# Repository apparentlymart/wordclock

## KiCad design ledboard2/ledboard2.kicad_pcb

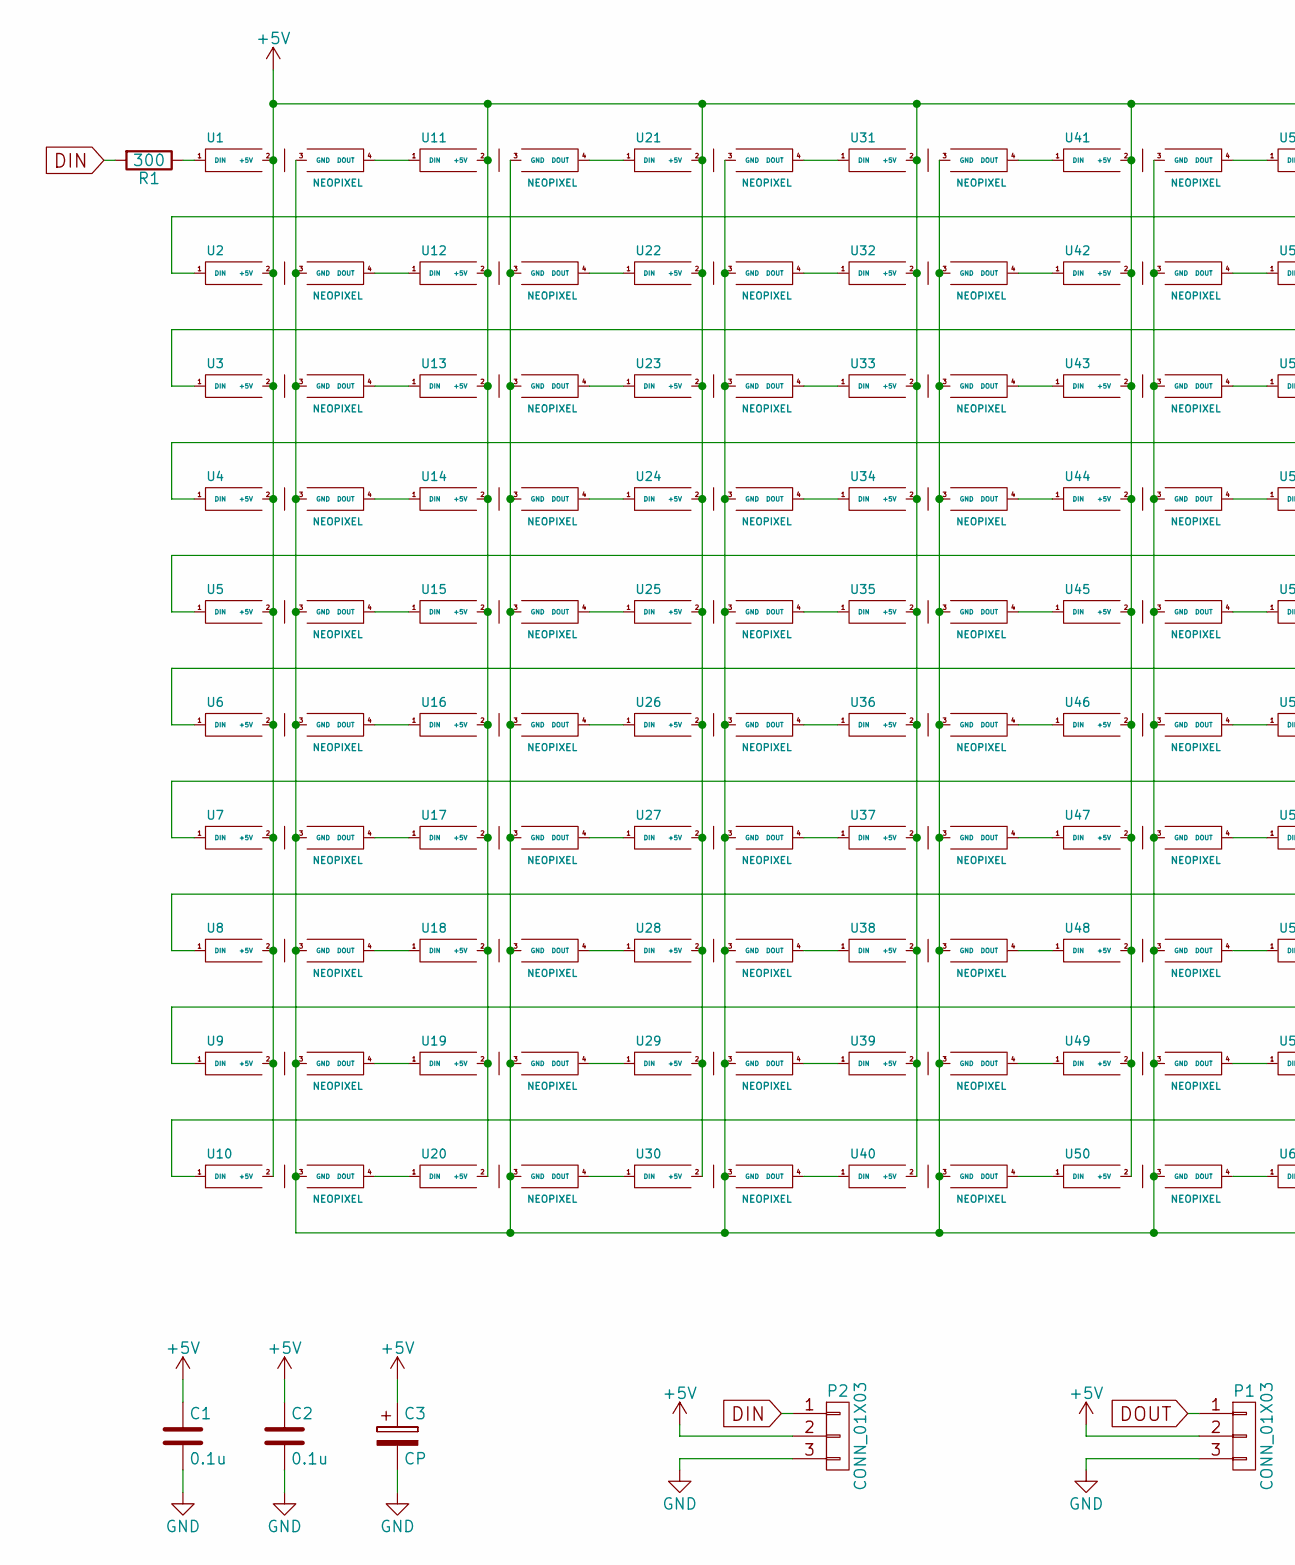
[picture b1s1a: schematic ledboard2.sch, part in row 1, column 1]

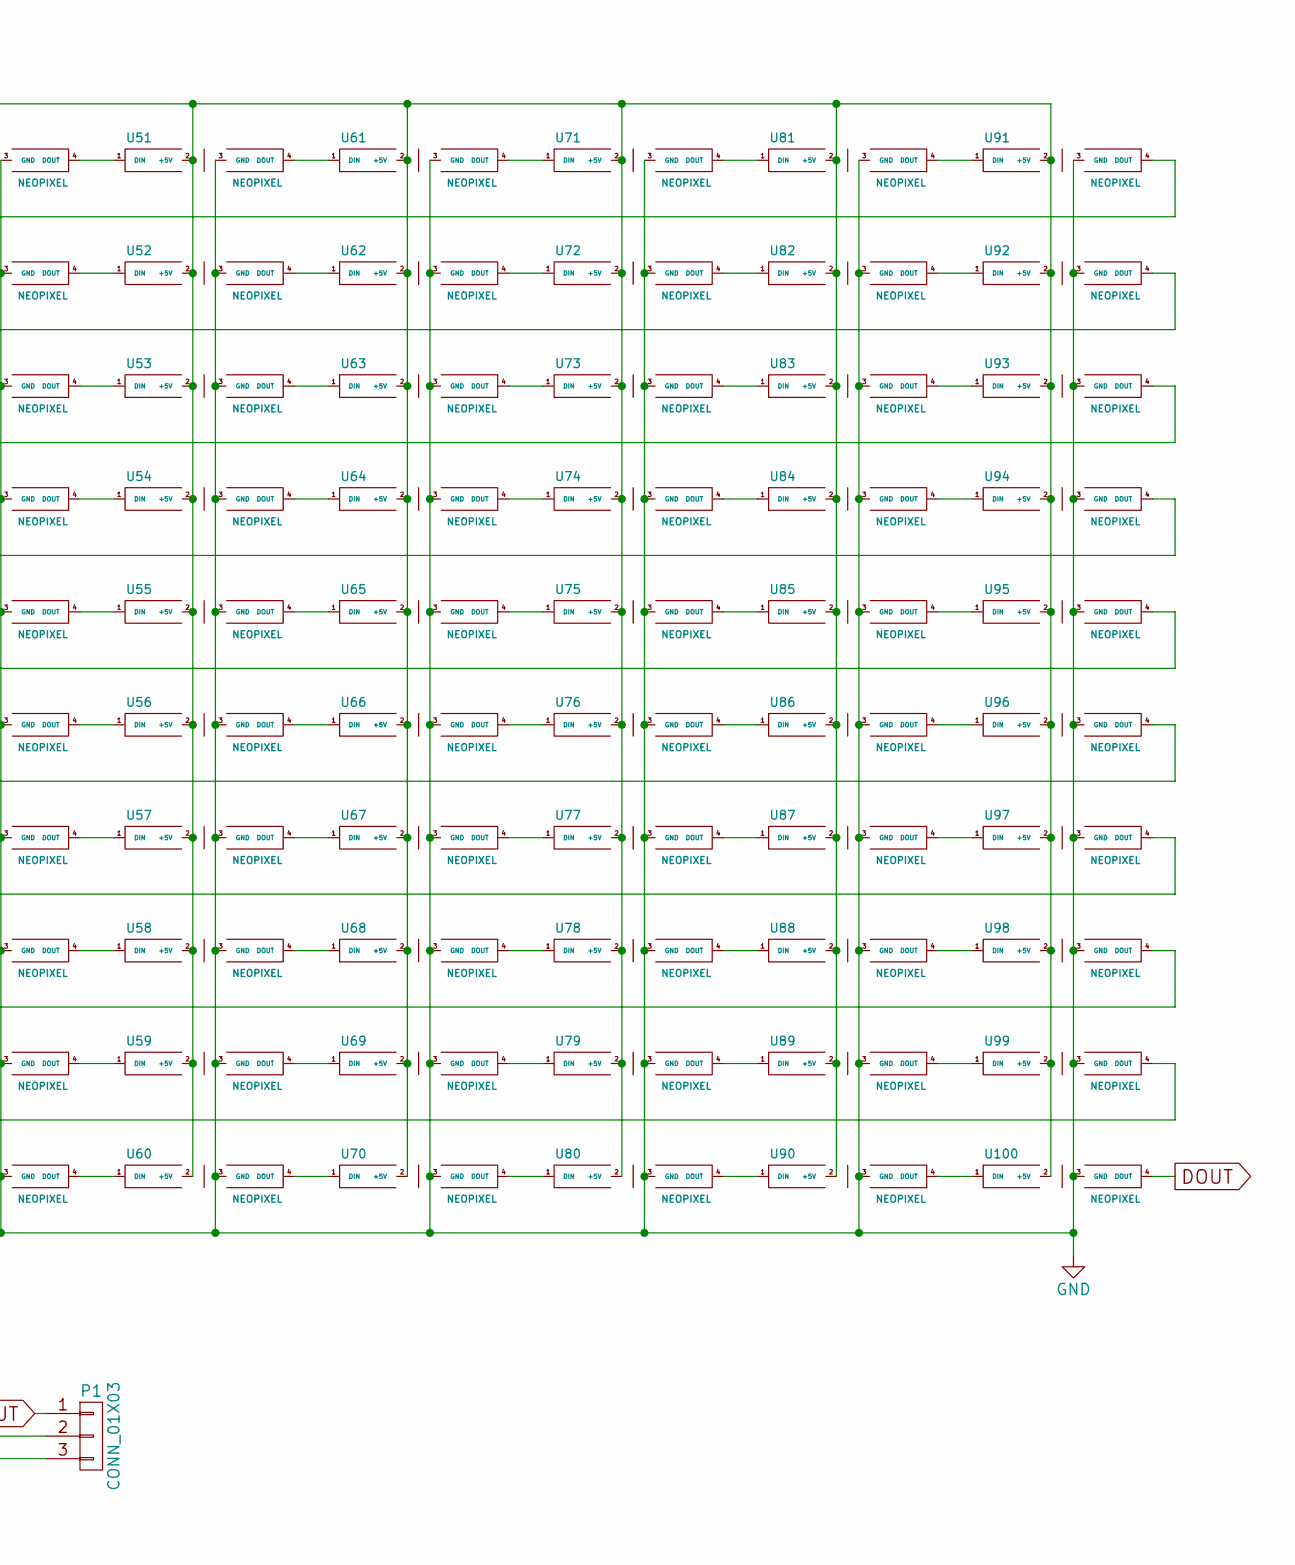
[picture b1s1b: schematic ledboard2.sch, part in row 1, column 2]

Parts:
C1, C2: 0.1u; C_0805_HandSoldering
C3: CP
P1, P2: CONN_01X03; Pin_Header_Straight_1x03
R1: 300; R_0805_HandSoldering
U1, U2, U3, U4, U5, U6, U7, U8, U9, U10, U11, U12, U13, U14, U15, U16, U17, U18, U19, U20, U21, U22, U23, U24, U25, U26, U27, U28, U29, U30, U31, U32, U33, U34, U35, U36, U37, U38, U39, U40, U41, U42, U43, U44, U45, U46, U47, U48, U49, U50, U51, U52, U53, U54, U55, U56, U57, U58, U59, U60, U61, U62, U63, U64, U65, U66, U67, U68, U69, U70, U71, U72, U73, U74, U75, U76, U77, U78, U79, U80, U81, U82, U83, U84, U85, U86, U87, U88, U89, U90, U91, U92, U93, U94, U95, U96, U97, U98, U99, U100: NEOPIXEL; NEOPIXEL_8MM

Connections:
+5V: C1.1, C2.1, C3.1, P1.2, P2.2, U1.2 (+5V), U2.2 (+5V), U3.2 (+5V), U4.2 (+5V), U5.2 (+5V), U6.2 (+5V), U7.2 (+5V), U8.2 (+5V), U9.2 (+5V), U10.2 (+5V), U11.2 (+5V), U12.2 (+5V), U13.2 (+5V), U14.2 (+5V), U15.2 (+5V), U16.2 (+5V), U17.2 (+5V), U18.2 (+5V), U19.2 (+5V), U20.2 (+5V), U21.2 (+5V), U22.2 (+5V), U23.2 (+5V), U24.2 (+5V), U25.2 (+5V), U26.2 (+5V), U27.2 (+5V), U28.2 (+5V), U29.2 (+5V), U30.2 (+5V), U31.2 (+5V), U32.2 (+5V), U33.2 (+5V), U34.2 (+5V), U35.2 (+5V), U36.2 (+5V), U37.2 (+5V), U38.2 (+5V), U39.2 (+5V), U40.2 (+5V), U41.2 (+5V), U42.2 (+5V), U43.2 (+5V), U44.2 (+5V), U45.2 (+5V), U46.2 (+5V), U47.2 (+5V), U48.2 (+5V), U49.2 (+5V), U50.2 (+5V), U51.2 (+5V), U52.2 (+5V), U53.2 (+5V), U54.2 (+5V), U55.2 (+5V), U56.2 (+5V), U57.2 (+5V), U58.2 (+5V), U59.2 (+5V), U60.2 (+5V), U61.2 (+5V), U62.2 (+5V), U63.2 (+5V), U64.2 (+5V), U65.2 (+5V), U66.2 (+5V), U67.2 (+5V), U68.2 (+5V), U69.2 (+5V), U70.2 (+5V), U71.2 (+5V), U72.2 (+5V), U73.2 (+5V), U74.2 (+5V), U75.2 (+5V), U76.2 (+5V), U77.2 (+5V), U78.2 (+5V), U79.2 (+5V), U80.2 (+5V), U81.2 (+5V), U82.2 (+5V), U83.2 (+5V), U84.2 (+5V), U85.2 (+5V), U86.2 (+5V), U87.2 (+5V), U88.2 (+5V), U89.2 (+5V), U90.2 (+5V), U91.2 (+5V), U92.2 (+5V), U93.2 (+5V), U94.2 (+5V), U95.2 (+5V), U96.2 (+5V), U97.2 (+5V), U98.2 (+5V), U99.2 (+5V), U100.2 (+5V)
DIN: P2.1, R1.2
DOUT: P1.1, U100.4 (DOUT)
GND: C1.2, C2.2, C3.2, P1.3, P2.3, U1.3 (GND), U2.3 (GND), U3.3 (GND), U4.3 (GND), U5.3 (GND), U6.3 (GND), U7.3 (GND), U8.3 (GND), U9.3 (GND), U10.3 (GND), U11.3 (GND), U12.3 (GND), U13.3 (GND), U14.3 (GND), U15.3 (GND), U16.3 (GND), U17.3 (GND), U18.3 (GND), U19.3 (GND), U20.3 (GND), U21.3 (GND), U22.3 (GND), U23.3 (GND), U24.3 (GND), U25.3 (GND), U26.3 (GND), U27.3 (GND), U28.3 (GND), U29.3 (GND), U30.3 (GND), U31.3 (GND), U32.3 (GND), U33.3 (GND), U34.3 (GND), U35.3 (GND), U36.3 (GND), U37.3 (GND), U38.3 (GND), U39.3 (GND), U40.3 (GND), U41.3 (GND), U42.3 (GND), U43.3 (GND), U44.3 (GND), U45.3 (GND), U46.3 (GND), U47.3 (GND), U48.3 (GND), U49.3 (GND), U50.3 (GND), U51.3 (GND), U52.3 (GND), U53.3 (GND), U54.3 (GND), U55.3 (GND), U56.3 (GND), U57.3 (GND), U58.3 (GND), U59.3 (GND), U60.3 (GND), U61.3 (GND), U62.3 (GND), U63.3 (GND), U64.3 (GND), U65.3 (GND), U66.3 (GND), U67.3 (GND), U68.3 (GND), U69.3 (GND), U70.3 (GND), U71.3 (GND), U72.3 (GND), U73.3 (GND), U74.3 (GND), U75.3 (GND), U76.3 (GND), U77.3 (GND), U78.3 (GND), U79.3 (GND), U80.3 (GND), U81.3 (GND), U82.3 (GND), U83.3 (GND), U84.3 (GND), U85.3 (GND), U86.3 (GND), U87.3 (GND), U88.3 (GND), U89.3 (GND), U90.3 (GND), U91.3 (GND), U92.3 (GND), U93.3 (GND), U94.3 (GND), U95.3 (GND), U96.3 (GND), U97.3 (GND), U98.3 (GND), U99.3 (GND), U100.3 (GND)
unnamed: R1.1, U1.1 (DIN)
unnamed: U1.4 (DOUT), U11.1 (DIN)
unnamed: U2.1 (DIN), U91.4 (DOUT)
unnamed: U3.1 (DIN), U92.4 (DOUT)
unnamed: U4.1 (DIN), U93.4 (DOUT)
unnamed: U5.1 (DIN), U94.4 (DOUT)
unnamed: U6.1 (DIN), U95.4 (DOUT)
unnamed: U7.1 (DIN), U96.4 (DOUT)
unnamed: U8.1 (DIN), U97.4 (DOUT)
unnamed: U9.1 (DIN), U98.4 (DOUT)
unnamed: U10.1 (DIN), U99.4 (DOUT)
unnamed: U10.4 (DOUT), U20.1 (DIN)
unnamed: U11.4 (DOUT), U21.1 (DIN)
unnamed: U2.4 (DOUT), U12.1 (DIN)
unnamed: U12.4 (DOUT), U22.1 (DIN)
unnamed: U3.4 (DOUT), U13.1 (DIN)
unnamed: U13.4 (DOUT), U23.1 (DIN)
unnamed: U4.4 (DOUT), U14.1 (DIN)
unnamed: U14.4 (DOUT), U24.1 (DIN)
unnamed: U5.4 (DOUT), U15.1 (DIN)
unnamed: U15.4 (DOUT), U25.1 (DIN)
unnamed: U6.4 (DOUT), U16.1 (DIN)
unnamed: U16.4 (DOUT), U26.1 (DIN)
unnamed: U7.4 (DOUT), U17.1 (DIN)
unnamed: U17.4 (DOUT), U27.1 (DIN)
unnamed: U8.4 (DOUT), U18.1 (DIN)
unnamed: U18.4 (DOUT), U28.1 (DIN)
unnamed: U9.4 (DOUT), U19.1 (DIN)
unnamed: U19.4 (DOUT), U29.1 (DIN)
unnamed: U20.4 (DOUT), U30.1 (DIN)
unnamed: U21.4 (DOUT), U31.1 (DIN)
unnamed: U22.4 (DOUT), U32.1 (DIN)
unnamed: U23.4 (DOUT), U33.1 (DIN)
unnamed: U24.4 (DOUT), U34.1 (DIN)
unnamed: U25.4 (DOUT), U35.1 (DIN)
unnamed: U26.4 (DOUT), U36.1 (DIN)
unnamed: U27.4 (DOUT), U37.1 (DIN)
unnamed: U28.4 (DOUT), U38.1 (DIN)
unnamed: U29.4 (DOUT), U39.1 (DIN)
unnamed: U30.4 (DOUT), U40.1 (DIN)
unnamed: U31.4 (DOUT), U41.1 (DIN)
unnamed: U32.4 (DOUT), U42.1 (DIN)
unnamed: U33.4 (DOUT), U43.1 (DIN)
unnamed: U34.4 (DOUT), U44.1 (DIN)
unnamed: U35.4 (DOUT), U45.1 (DIN)
unnamed: U36.4 (DOUT), U46.1 (DIN)
unnamed: U37.4 (DOUT), U47.1 (DIN)
unnamed: U38.4 (DOUT), U48.1 (DIN)
unnamed: U39.4 (DOUT), U49.1 (DIN)
unnamed: U40.4 (DOUT), U50.1 (DIN)
unnamed: U41.4 (DOUT), U51.1 (DIN)
unnamed: U42.4 (DOUT), U52.1 (DIN)
unnamed: U43.4 (DOUT), U53.1 (DIN)
unnamed: U44.4 (DOUT), U54.1 (DIN)
unnamed: U45.4 (DOUT), U55.1 (DIN)
unnamed: U46.4 (DOUT), U56.1 (DIN)
unnamed: U47.4 (DOUT), U57.1 (DIN)
unnamed: U48.4 (DOUT), U58.1 (DIN)
unnamed: U49.4 (DOUT), U59.1 (DIN)
unnamed: U50.4 (DOUT), U60.1 (DIN)
unnamed: U51.4 (DOUT), U61.1 (DIN)
unnamed: U52.4 (DOUT), U62.1 (DIN)
unnamed: U53.4 (DOUT), U63.1 (DIN)
unnamed: U54.4 (DOUT), U64.1 (DIN)
unnamed: U55.4 (DOUT), U65.1 (DIN)
unnamed: U56.4 (DOUT), U66.1 (DIN)
unnamed: U57.4 (DOUT), U67.1 (DIN)
unnamed: U58.4 (DOUT), U68.1 (DIN)
unnamed: U59.4 (DOUT), U69.1 (DIN)
unnamed: U60.4 (DOUT), U70.1 (DIN)
unnamed: U61.4 (DOUT), U71.1 (DIN)
unnamed: U62.4 (DOUT), U72.1 (DIN)
unnamed: U63.4 (DOUT), U73.1 (DIN)
unnamed: U64.4 (DOUT), U74.1 (DIN)
unnamed: U65.4 (DOUT), U75.1 (DIN)
unnamed: U66.4 (DOUT), U76.1 (DIN)
unnamed: U67.4 (DOUT), U77.1 (DIN)
unnamed: U68.4 (DOUT), U78.1 (DIN)
unnamed: U69.4 (DOUT), U79.1 (DIN)
unnamed: U70.4 (DOUT), U80.1 (DIN)
unnamed: U71.4 (DOUT), U81.1 (DIN)
unnamed: U72.4 (DOUT), U82.1 (DIN)
unnamed: U73.4 (DOUT), U83.1 (DIN)
unnamed: U74.4 (DOUT), U84.1 (DIN)
unnamed: U75.4 (DOUT), U85.1 (DIN)
unnamed: U76.4 (DOUT), U86.1 (DIN)
unnamed: U77.4 (DOUT), U87.1 (DIN)
unnamed: U78.4 (DOUT), U88.1 (DIN)
unnamed: U79.4 (DOUT), U89.1 (DIN)
unnamed: U80.4 (DOUT), U90.1 (DIN)
unnamed: U81.4 (DOUT), U91.1 (DIN)
unnamed: U82.4 (DOUT), U92.1 (DIN)
unnamed: U83.4 (DOUT), U93.1 (DIN)
unnamed: U84.4 (DOUT), U94.1 (DIN)
unnamed: U85.4 (DOUT), U95.1 (DIN)
unnamed: U86.4 (DOUT), U96.1 (DIN)
unnamed: U87.4 (DOUT), U97.1 (DIN)
unnamed: U88.4 (DOUT), U98.1 (DIN)
unnamed: U89.4 (DOUT), U99.1 (DIN)
unnamed: U90.4 (DOUT), U100.1 (DIN)

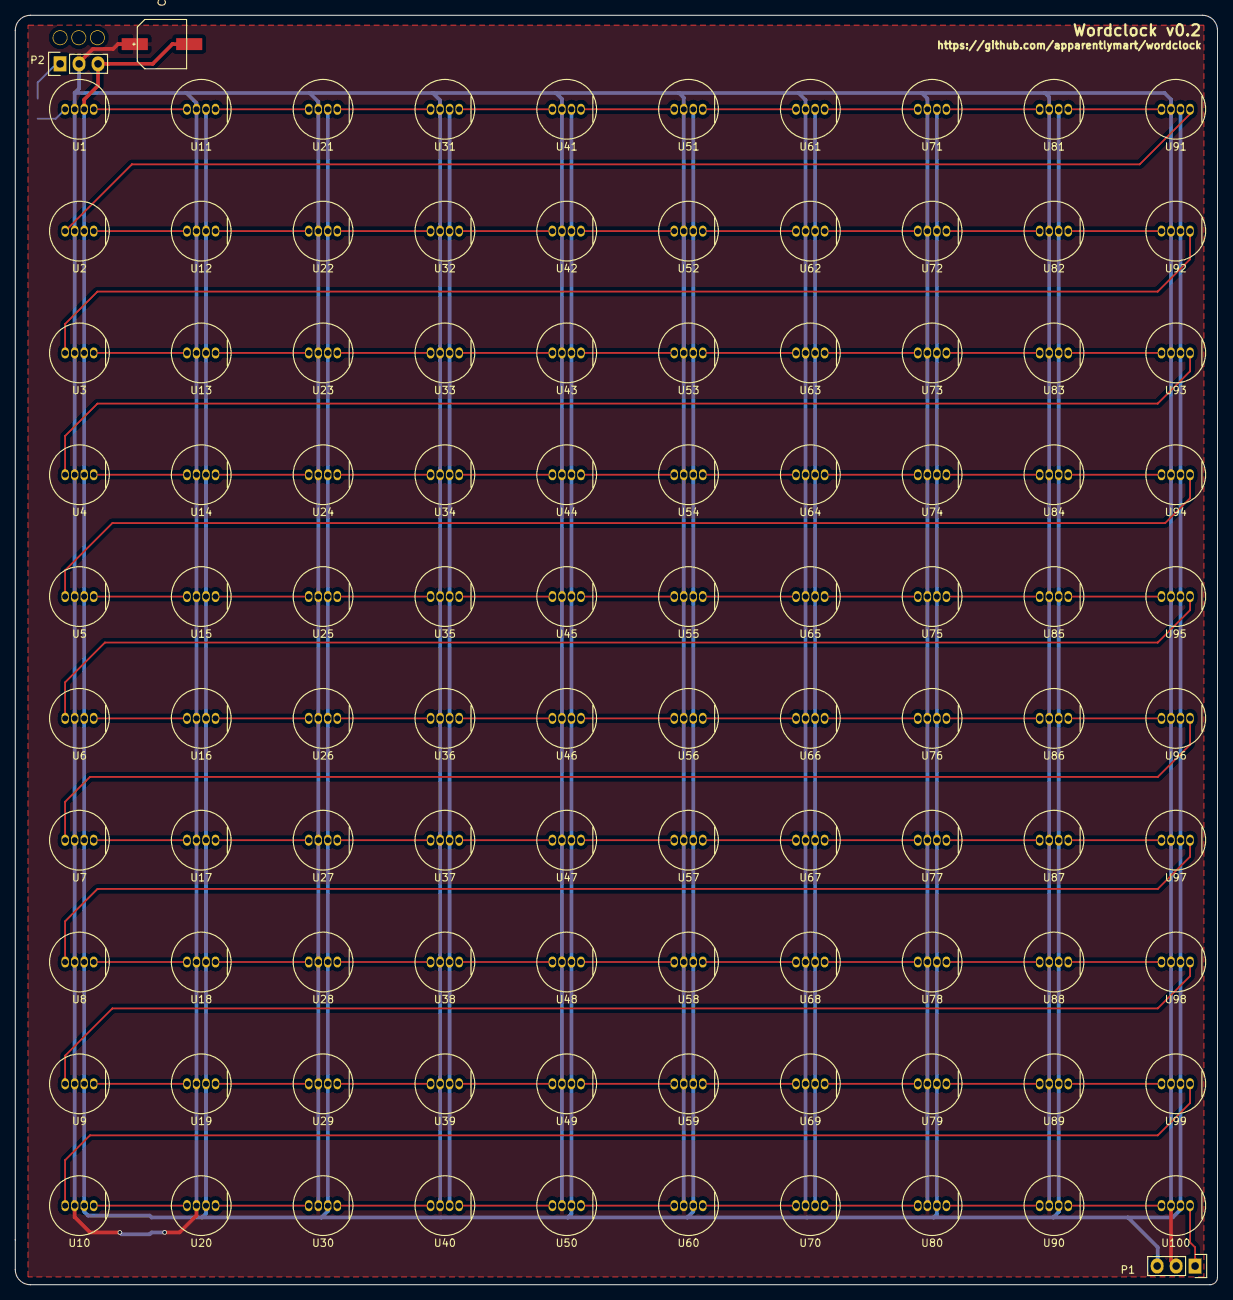
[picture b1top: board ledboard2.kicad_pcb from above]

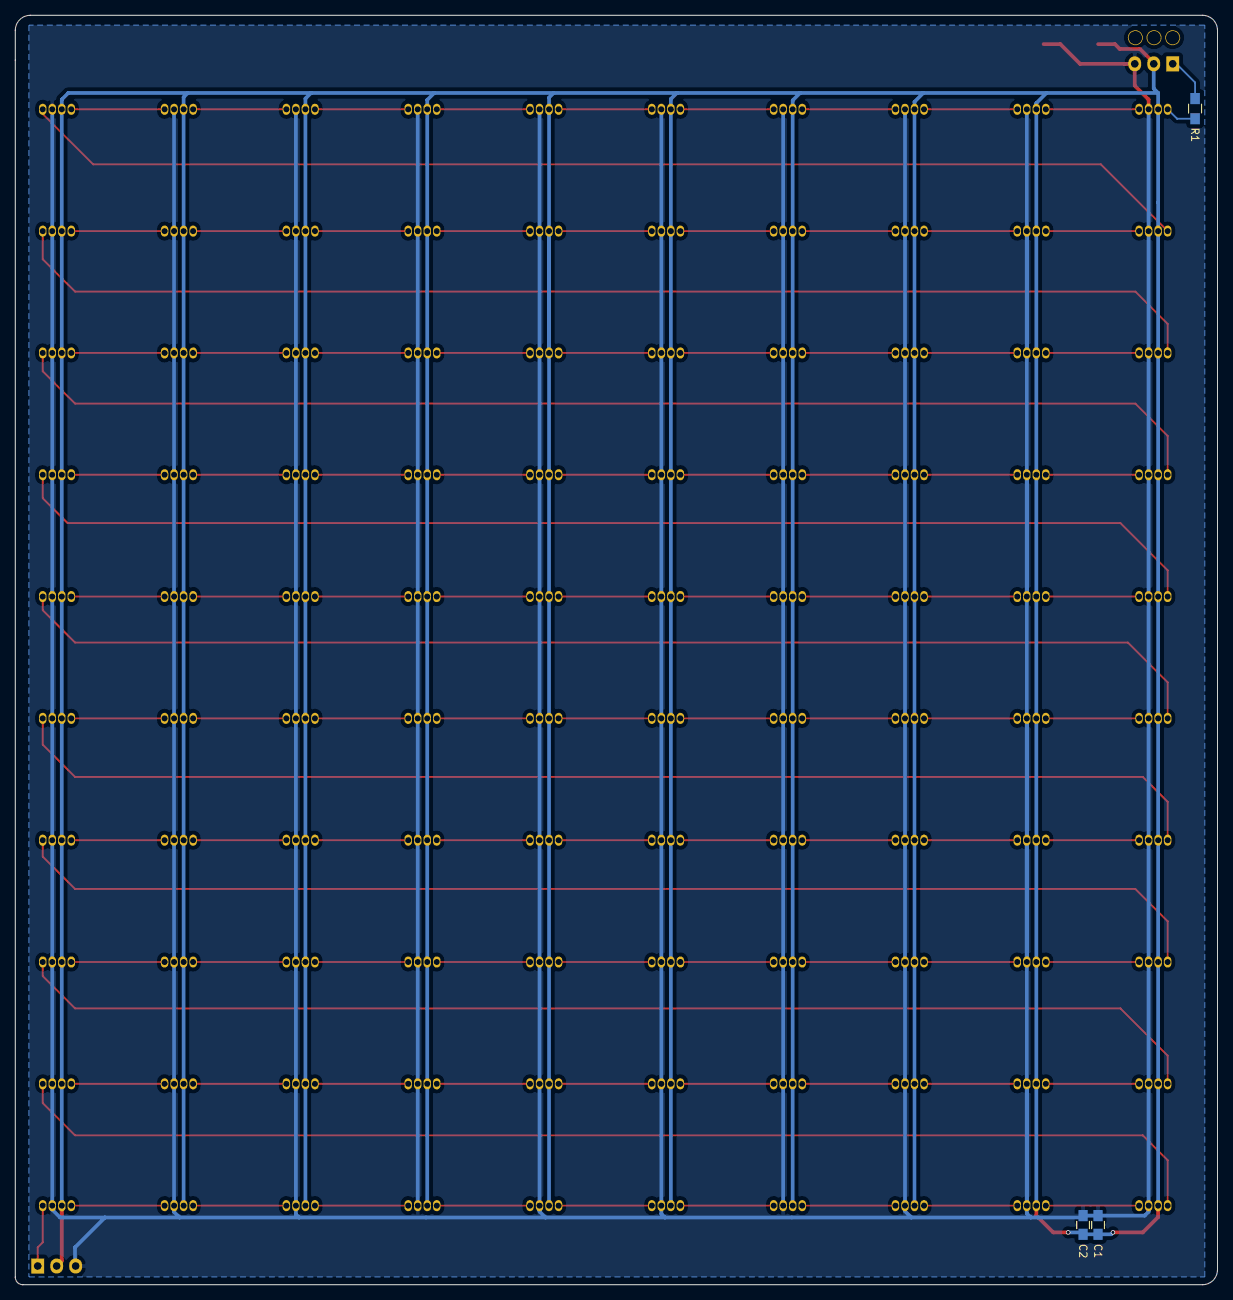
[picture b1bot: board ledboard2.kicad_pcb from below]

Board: 2 copper layers, 161.0 x 170.0 mm, 106 parts (3 on the bottom side), 104 nets.

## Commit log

2013-09-14 prototyping.
    The major failing of this prototype is that I forgot to include "TWELVE"
    in the word matrix, so the next iteration of this will require some
    changes in that regard.
2013-09-15 Better prototype which can actually say TWELVE.
    Got rid of the "IT IS" words; they're not very interesting anyway since
    they are just always illuminated. We can still say
    TIME TO EAT / SLEEP / GO / WAKE UP as well as actual time readouts.
2013-09-15 Hacked up script to make an SVG of the letters to print.
    What it generates is not quite aligned properly so it needs some manual
    post-processing before printing.
2013-09-16 Notes about a config that takes only 9x9 LEDs
2013-12-08 PCB design for a 9x9 "neopixel" board.
2014-04-14 Add some notes about wordclocks in other languages.
    Summary: looks like 9x9 is a sweet spot for English, but not for French,
    German or Spanish. Would need to grow a bit to support other languages
    on the same hardware. Not tried 10x10 yet, but we know that ended up
    a little *too* spacious for English.
2014-04-14 Expanding to 10x10 makes it work for French, German and Spanish too.
    No such luck with Latin or Russian, since the related vocabulary there
    doesn't have many words that can overlap to save space.
2014-12-01 Two new design files for the latest iteration of the design.
2015-07-06 New PCB for a NeoPixel matrix.
2015-07-06 Move the board bits into the diagram borders.
2015-07-06 Edge cuts
2015-07-06 Final tweaks before ordering v0.1 PCBs.
2015-09-07 Increase NeoPixel hole sizes and add bigger capacitor.
2015-09-07 Add filled zones.
    These aren't really serving any electrical purpose, but since these boards
    are being manufactured very thin they are quite translucent where no
    copper is present.
2015-09-07 Bump revision to v0.2.
2015-09-07 Tweak the pad sizes on the Neopixel footprints.
    Making them a little narrower but a lot taller should make them less
    likely to short while easier to solder.
2015-09-07 SMD polarized capacitor footprint.
2015-09-07 More hole/pad tweaking for the NeoPixels.
    The tolerances here are pretty tight, but this now just about satisfies
    the design rules at Seeedstudio.
